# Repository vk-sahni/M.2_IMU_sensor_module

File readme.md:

# M.2 RP2350 IMU Sensor Module

A KiCad hardware design for a compact M.2 Key A sensor module built around the Raspberry Pi RP2350B. The board combines an MPU-9250 motion sensor and a BME280 environmental sensor, with UAV and ArduPilot integration as the intended use case.

> **Project status:** Work in progress. The repository contains KiCad design files only; it does not include firmware or establish plug-and-play ArduPilot compatibility. The current design has outstanding KiCad ERC/DRC violations and is not ready for fabrication or flight use.

## GitHub repository description

> KiCad design for an M.2 Key A RP2350B sensor module featuring an MPU-9250 IMU and BME280, intended for UAV and ArduPilot integration experiments.

## Design overview

- **MCU:** RP2350B
- **IMU:** MPU-9250 (accelerometer, gyroscope, and magnetometer)
- **Environmental sensor:** BME280 (pressure, temperature, and humidity)
- **Memory:** W25Q128JVSIQ QSPI flash and APS6404L PSRAM
- **Removable storage:** MicroSD card socket
- **Host connection:** M.2 Key A edge connector
- **Other interfaces:** USB Type-C, SWD test points, and status LEDs
- **Power:** On-board XC6220 3.3 V regulators

The M.2 connector schematic maps 5 V power and sensor I2C signals, including separate `SDA`/`SCL` and `MPU_SDA`/`MPU_SCL` nets. Check the full schematic and target host pinout before connecting the module; M.2 is a connector format, not a guarantee of electrical or firmware compatibility.

## ArduPilot integration

This is a hardware design intended for UAV sensor and ArduPilot integration experiments. ArduPilot supports sensor communications over protocols such as I2C, SPI, UART, and CAN, but a sensor board still needs a compatible driver/backend, wiring, and configuration. This repository does not contain that firmware integration or demonstrate that an ArduPilot flight controller can detect these sensors through this M.2 connection.

Before attempting integration, verify the M.2 host pinout and voltage levels, determine which controller owns each bus, and confirm that the target ArduPilot firmware supports the required sensors and connection arrangement. See the official [ArduPilot sensor-driver documentation](https://ardupilot.org/dev/docs/code-overview-sensor-drivers.html).

## Repository contents

- `PCIe_Pie.kicad_pro` — KiCad project settings
- `PCIe_Pie.kicad_sch` and the other `*.kicad_sch` files — top-level and hierarchical schematics
- `PCIe_Pie.kicad_pcb` — PCB layout
- `CM4IO.pretty/` — project footprint library
- `CM4IO.3dshapes/` — 3D models used by footprints
- `sym-lib-table`, `fp-lib-table` — KiCad library table configuration

## Open the design

1. Install KiCad.
2. Open `PCIe_Pie.kicad_pro`.
3. Review the complete schematic hierarchy and PCB, including the project-local footprint and 3D model libraries.

## Validation status

KiCad command-line ERC and DRC checks run against the current design reported outstanding violations, including unconnected items. Review and resolve these in KiCad before generating manufacturing files. No fabrication outputs, assembled-board test results, sensor calibration results, or flight-test results are included in this repository.

## Safety

Treat the design as experimental. Verify the schematic, PCB rules, power rails, connector orientation, and signal levels before powering hardware. Bench-test and validate the complete sensor/firmware path before any UAV flight; do not rely on this module as a flight-critical sensor without appropriate testing and failsafes.

## References

- [ArduPilot sensor drivers and supported communication protocols](https://ardupilot.org/dev/docs/code-overview-sensor-drivers.html)
- [MPU-9250 datasheet](https://invensense.tdk.com/wp-content/uploads/2015/02/PS-MPU-9250A-01-v1.1.pdf)

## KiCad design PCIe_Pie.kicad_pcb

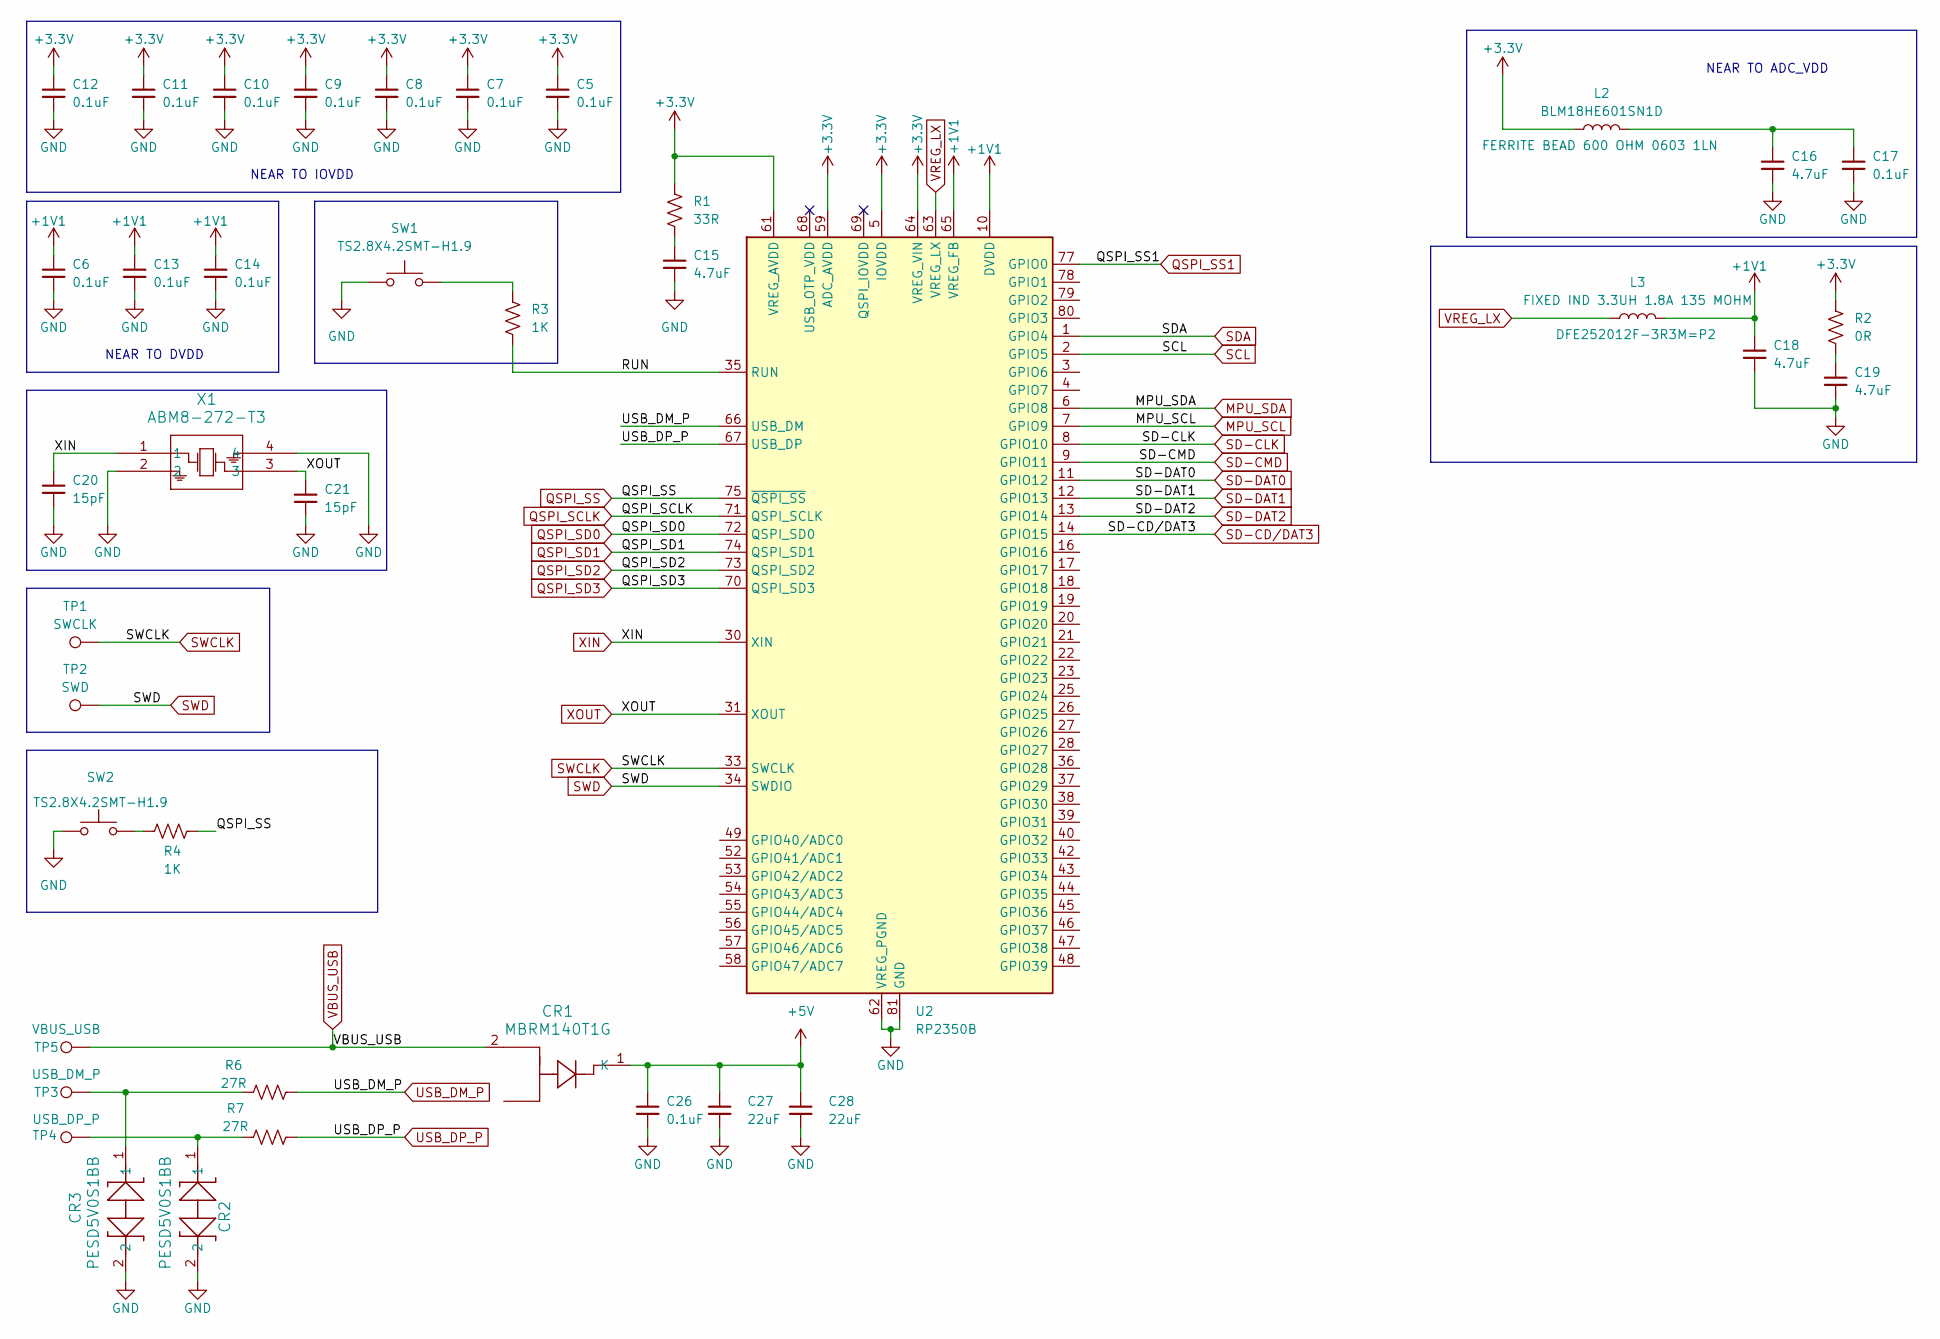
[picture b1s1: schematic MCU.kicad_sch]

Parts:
C5, C6, C7, C8, C9, C10, C11, C12, C13, C14, C17, C26: 0.1uF; C_0402_1005Metric
C15, C16, C18, C19: 4.7uF; C_0402_1005Metric
C20, C21: 15pF; C_0402_1005Metric
C27, C28: 22uF; C_0402_1005Metric
CR1: MBRM140T1G; CR_POWERMITE_457-04_ONS-L
CR2, CR3: PESD5V0S1BB; SOD523_NXP-L
L2: BLM18HE601SN1D; L_0402_1005Metric; PART FERRITE BEAD 600 OHM 0603 1LN
L3: FIXED IND 3.3UH 1.8A 135 MOHM; L_0402_1005Metric; PART DFE252012F-3R3M=P2
R1: 33R; R_0402_1005Metric
R2: 0R; R_0402_1005Metric
R3, R4: 1K; R_0402_1005Metric
R6, R7: 27R; R_0402_1005Metric
SW1, SW2: TS2.8X4.2SMT-H1.9; SW_Push_SPST_NO_Alps_SKRK
TP1: SWCLK; TestPoint_Pad_1.0x1.0mm
TP2: SWD; TestPoint_Pad_1.0x1.0mm
TP3: USB_DM_P; TestPoint_Pad_1.0x1.0mm
TP4: USB_DP_P; TestPoint_Pad_1.0x1.0mm
TP5: VBUS_USB; TestPoint_Pad_1.0x1.0mm
U2: RP2350B; QFN-80-1EP_10x10mm_P0.4mm_EP3.4x3.4mm
X1: ABM8-272-T3; ABM8-272-T3_ABR

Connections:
+1V1: C6.1, C13.1, C14.1, C18.1, L3.2, U2.10 (DVDD), U2.32 (DVDD), U2.51 (DVDD), U2.65 (VREG_FB)
+3.3V: C5.1, C7.1, C8.1, C9.1, C10.1, C11.1, C12.1, L2.1, R1.1, R2.1, U2.5 (IOVDD), U2.15 (IOVDD), U2.24 (IOVDD), U2.29 (IOVDD), U2.41 (IOVDD), U2.50 (IOVDD), U2.59 (ADC_AVDD), U2.60 (IOVDD), U2.61 (VREG_AVDD), U2.64 (VREG_VIN), U2.76 (IOVDD); also elsewhere on the board
+5V: C26.1, C27.1, C28.1, CR1.1 (K_1); also elsewhere on the board
/MCU/RUN: R3.2, U2.35 (RUN)
GND: C5.2, C6.2, C7.2, C8.2, C9.2, C10.2, C11.2, C12.2, C13.2, C14.2, C15.2, C16.2, C17.2, C18.2, C19.2, C20.2, C21.2, C26.2, C27.2, C28.2, CR2.2, CR3.2, SW1.1, SW2.1, U2.62 (VREG_PGND), U2.81 (GND), X1.2, X1.4; also elsewhere on the board
MPU_SCL: U2.7 (GPIO9); also elsewhere on the board
MPU_SDA: U2.6 (GPIO8); also elsewhere on the board
unnamed: C15.1, R1.2
unnamed: C16.1, C17.1, L2.2
unnamed: C19.1, R2.2
unnamed: CR2.1, R7.1, TP4.1 (1_1)
unnamed: CR3.1, R6.1, TP3.1 (1_1)
unnamed: R3.1, SW1.2
unnamed: R4.1, SW2.2
QSPI_SCLK: U2.71 (QSPI_SCLK); also elsewhere on the board
QSPI_SD0: U2.72 (QSPI_SD0); also elsewhere on the board
QSPI_SD1: U2.74 (QSPI_SD1); also elsewhere on the board
QSPI_SD2: U2.73 (QSPI_SD2); also elsewhere on the board
QSPI_SD3: U2.70 (QSPI_SD3); also elsewhere on the board
QSPI_SS: R4.2, U2.75 (~QSPI_SS); also elsewhere on the board
QSPI_SS1: U2.77 (GPIO0); also elsewhere on the board
SCL: U2.2 (GPIO5); also elsewhere on the board
SD-CD/DAT3: U2.14 (GPIO15); also elsewhere on the board
SD-CLK: U2.8 (GPIO10); also elsewhere on the board
SD-CMD: U2.9 (GPIO11); also elsewhere on the board
SD-DAT0: U2.11 (GPIO12); also elsewhere on the board
SD-DAT1: U2.12 (GPIO13); also elsewhere on the board
SD-DAT2: U2.13 (GPIO14); also elsewhere on the board
SDA: U2.1 (GPIO4); also elsewhere on the board
SWCLK: TP1.1 (1_1), U2.33 (SWCLK)
SWD: TP2.1 (1_1), U2.34 (SWDIO)
USB_DM_P: R6.2, U2.66 (USB_DM); also elsewhere on the board
USB_DP_P: R7.2, U2.67 (USB_DP); also elsewhere on the board
VBUS_USB: CR1.2, TP5.1 (1_1); also elsewhere on the board
VREG_LX: L3.1, U2.63 (VREG_LX)
XIN: C20.1, U2.30 (XIN), X1.1
XOUT: C21.1, U2.31 (XOUT), X1.3

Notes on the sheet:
NEAR TO ADC_VDD
NEAR TO IOVDD
NEAR TO DVDD

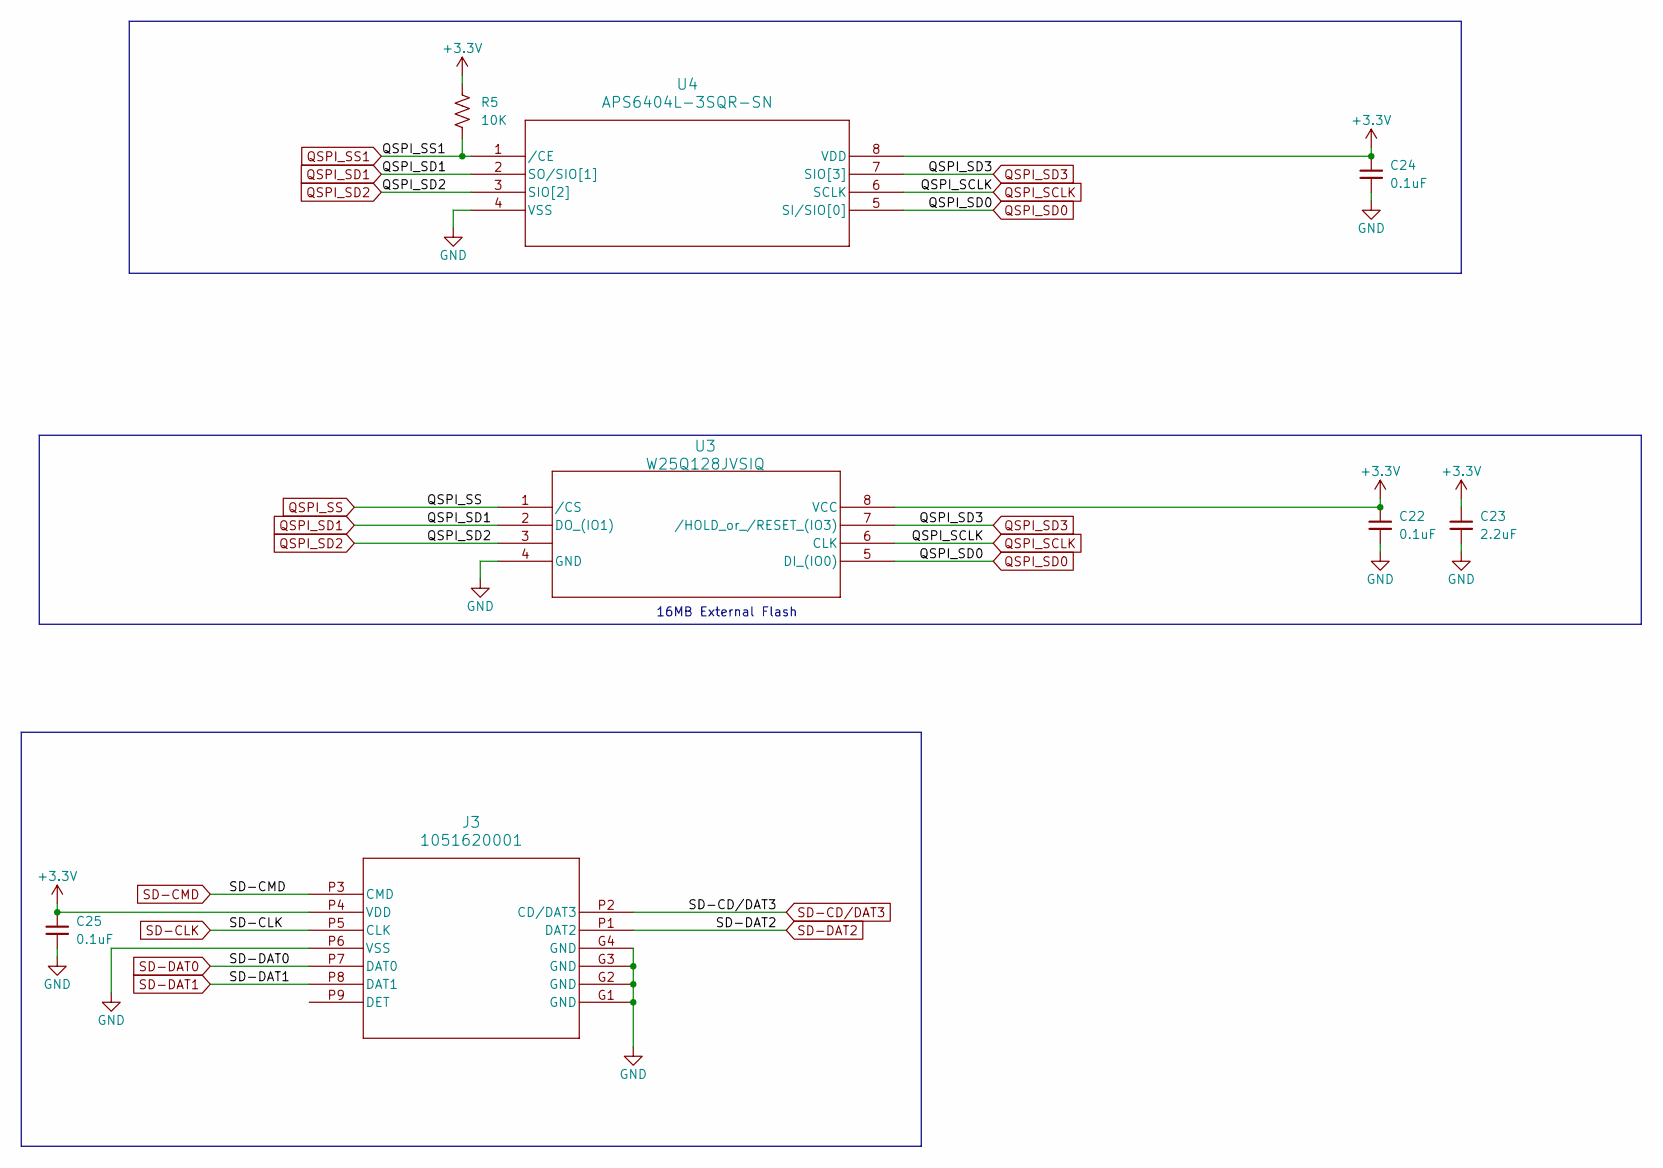
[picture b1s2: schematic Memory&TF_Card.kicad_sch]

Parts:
C22, C24, C25: 0.1uF; C_0402_1005Metric
C23: 2.2uF; C_0402_1005Metric
J3: 1051620001; 105162-0001_MOL
R5: 10K; R_0402_1005Metric
U3: W25Q128JVSIQ; SOIC_128JVSIQ_WIN-M
U4: APS6404L-3SQR-SN; APS6404L-3SQR-SN_APY-M

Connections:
+3.3V: C22.1, C23.1, C24.1, C25.1, J3.P4 (VDD), R5.1, U3.8 (VCC), U4.8 (VDD); also elsewhere on the board
GND: C22.2, C23.2, C24.2, C25.2, J3.G1 (GND), J3.G2 (GND), J3.G3 (GND), J3.G4 (GND), J3.P6 (VSS), U3.4 (GND), U4.4 (VSS); also elsewhere on the board
QSPI_SCLK: U3.6 (CLK), U4.6 (SCLK); also elsewhere on the board
QSPI_SD0: U3.5 (DI_(IO0)), U4.5 (SI/SIO[0]); also elsewhere on the board
QSPI_SD1: U3.2 (DO_(IO1)), U4.2 (SO/SIO[1]); also elsewhere on the board
QSPI_SD2: U3.3, U4.3 (SIO[2]); also elsewhere on the board
QSPI_SD3: U3.7 (/HOLD_or_/RESET_(IO3)), U4.7 (SIO[3]); also elsewhere on the board
QSPI_SS: U3.1 (/CS); also elsewhere on the board
QSPI_SS1: R5.2, U4.1 (/CE); also elsewhere on the board
SD-CD/DAT3: J3.P2 (CD/DAT3); also elsewhere on the board
SD-CLK: J3.P5 (CLK); also elsewhere on the board
SD-CMD: J3.P3 (CMD); also elsewhere on the board
SD-DAT0: J3.P7 (DAT0); also elsewhere on the board
SD-DAT1: J3.P8 (DAT1); also elsewhere on the board
SD-DAT2: J3.P1 (DAT2); also elsewhere on the board

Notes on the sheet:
16MB External Flash

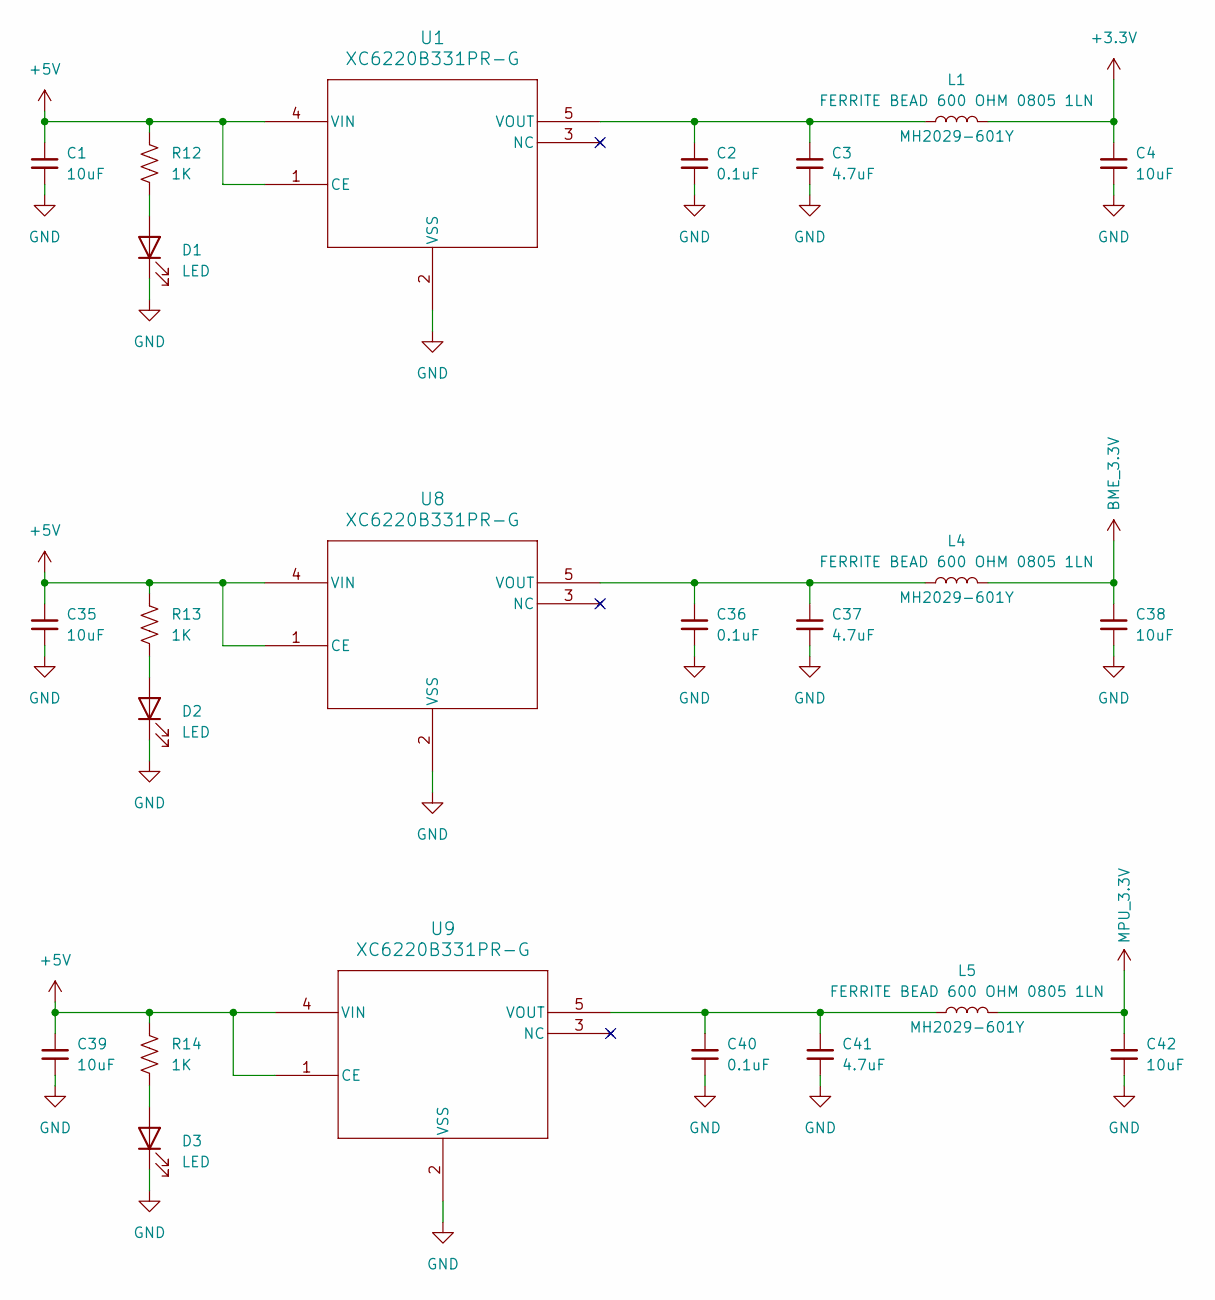
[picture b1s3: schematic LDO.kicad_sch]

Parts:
C1, C35, C39: 10uF; C_0805_2012Metric
C2, C36, C40: 0.1uF; C_0402_1005Metric
C3, C37, C41: 4.7uF; C_0402_1005Metric
C4, C38, C42: 10uF; C_0402_1005Metric
D1, D2, D3: LED; LED_0402_1005Metric
L1, L4, L5: FERRITE BEAD 600 OHM 0805 1LN; L_0402_1005Metric; Part MH2029-601Y
R12, R13, R14: 1K; R_0402_1005Metric
U1, U8, U9: XC6220B331PR-G; SOT-89-5_TOR

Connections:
+3.3V: C4.1, L1.2; also elsewhere on the board
+5V: C1.1, C35.1, C39.1, R12.1, R13.1, R14.1, U1.1 (CE), U1.4 (VIN), U8.1 (CE), U8.4 (VIN), U9.1 (CE), U9.4 (VIN); also elsewhere on the board
BME_3.3V: C38.1, L4.2; also elsewhere on the board
GND: C1.2, C2.2, C3.2, C4.2, C35.2, C36.2, C37.2, C38.2, C39.2, C40.2, C41.2, C42.2, D1.1 (K), D2.1 (K), D3.1 (K), U1.2 (VSS), U8.2 (VSS), U9.2 (VSS); also elsewhere on the board
MPU_3.3V: C42.1, L5.2; also elsewhere on the board
unnamed: D1.2 (A), R12.2
unnamed: D2.2 (A), R13.2
unnamed: D3.2 (A), R14.2
unnamed: C2.1, C3.1, L1.1, U1.5 (VOUT)
unnamed: C36.1, C37.1, L4.1, U8.5 (VOUT)
unnamed: C40.1, C41.1, L5.1, U9.5 (VOUT)

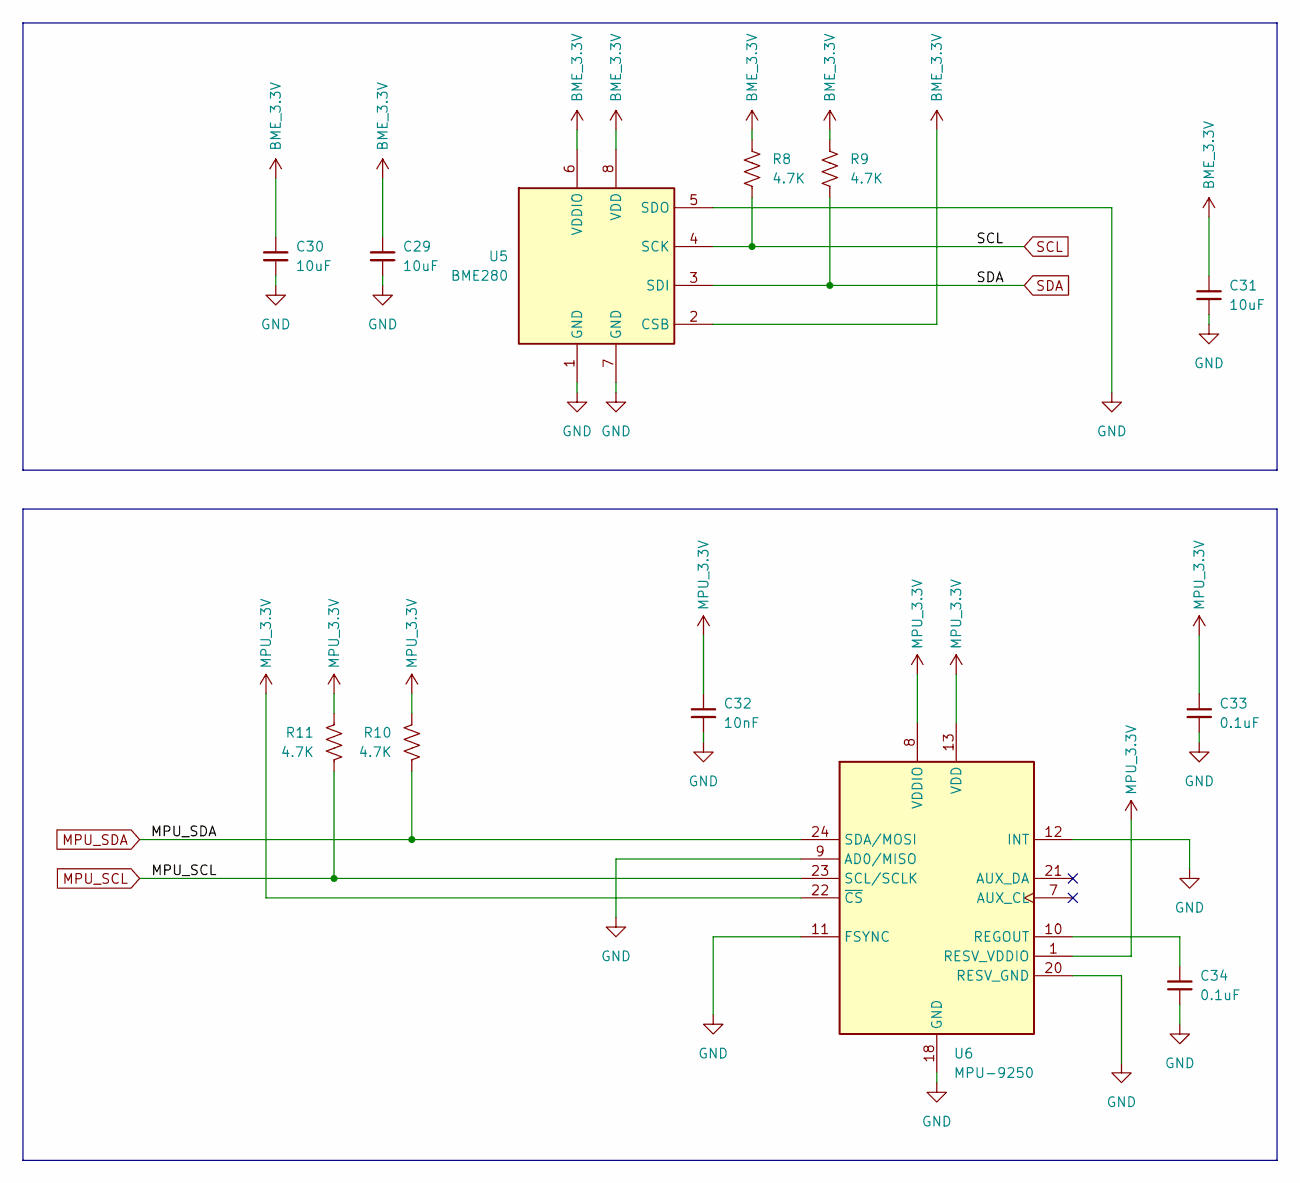
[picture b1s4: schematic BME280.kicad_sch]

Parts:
C29, C30, C31: 10uF; C_0402_1005Metric
C32: 10nF; C_0402_1005Metric
C33, C34: 0.1uF; C_0402_1005Metric
R8, R9, R10, R11: 4.7K; R_0402_1005Metric
U5: BME280; Bosch_LGA-8_2.5x2.5mm_P0.65mm_ClockwisePinNumbering
U6: MPU-9250; InvenSense_QFN-24_3x3mm_P0.4mm

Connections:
BME_3.3V: C29.1, C30.1, C31.1, R8.1, R9.1, U5.2 (CSB), U5.6 (VDDIO), U5.8 (VDD); also elsewhere on the board
GND: C29.2, C30.2, C31.2, C32.2, C33.2, C34.2, U5.1 (GND), U5.5 (SDO), U5.7 (GND), U6.9 (AD0/MISO), U6.11 (FSYNC), U6.12 (INT), U6.18 (GND), U6.20 (RESV_GND); also elsewhere on the board
MPU_3.3V: C32.1, C33.1, R10.1, R11.1, U6.1 (RESV_VDDIO), U6.8 (VDDIO), U6.13 (VDD), U6.22 (~CS); also elsewhere on the board
MPU_SCL: R11.2, U6.23 (SCL/SCLK); also elsewhere on the board
MPU_SDA: R10.2, U6.24 (SDA/MOSI); also elsewhere on the board
unnamed: C34.1, U6.10 (REGOUT)
SCL: R8.2, U5.4 (SCK); also elsewhere on the board
SDA: R9.2, U5.3 (SDI); also elsewhere on the board

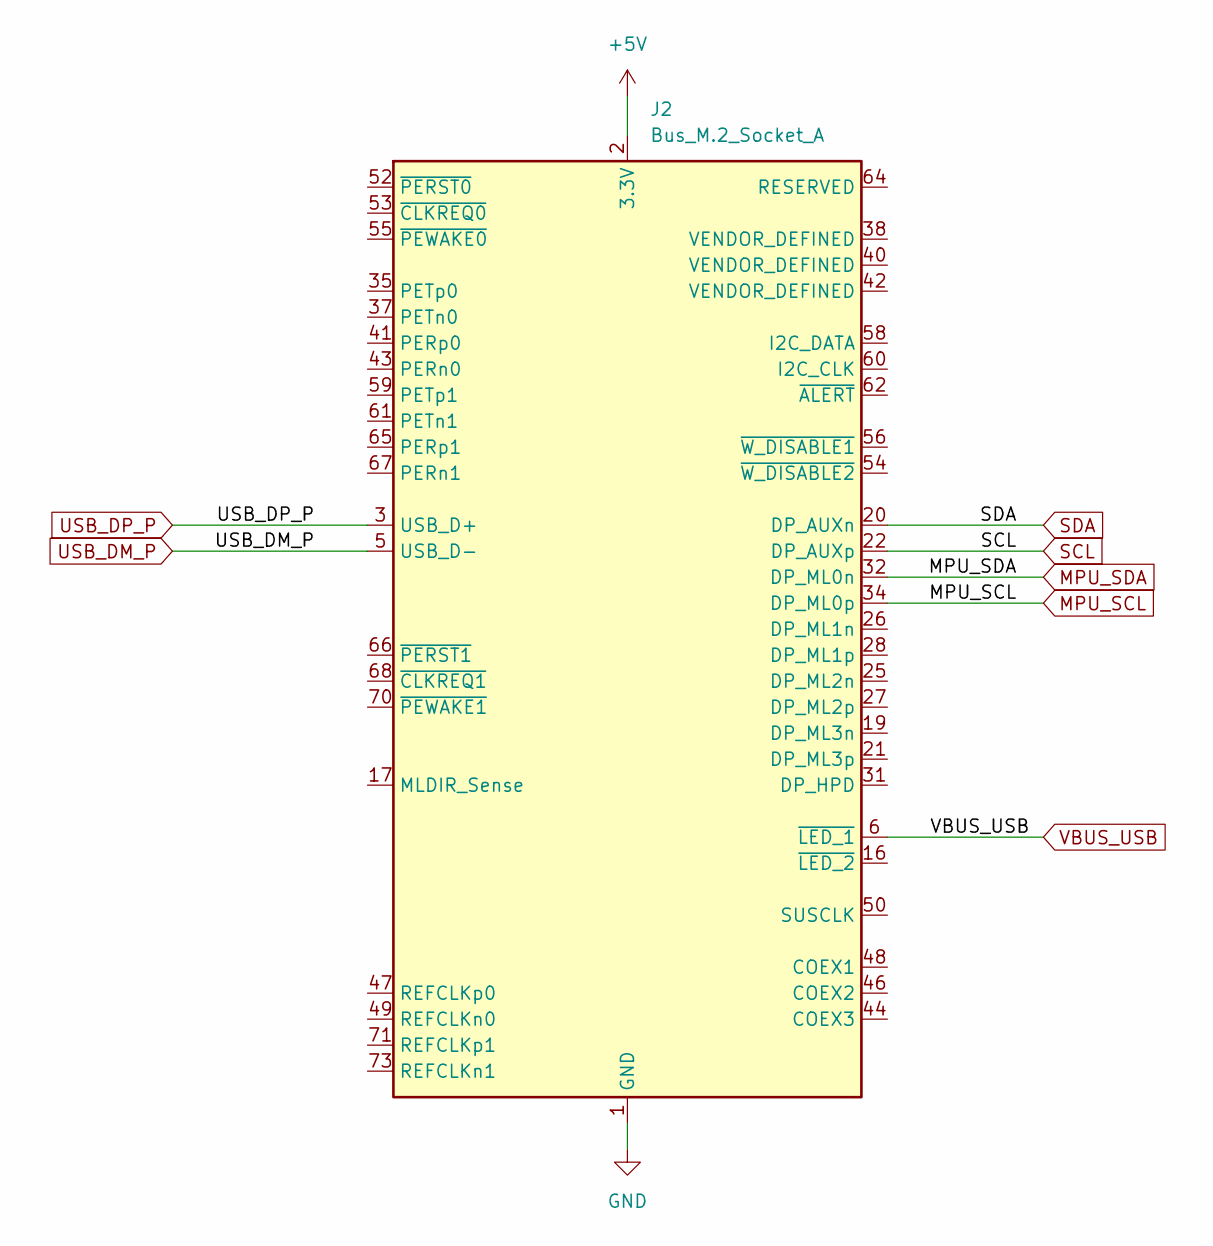
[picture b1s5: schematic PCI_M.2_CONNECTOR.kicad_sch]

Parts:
J2: Bus_M.2_Socket_A; M.2_3030-xx-A

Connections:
+5V: J2.2 (3.3V), J2.4 (3.3V), J2.72 (3.3V), J2.74 (3.3V); also elsewhere on the board
GND: J2.1 (GND), J2.7 (GND), J2.18 (GND), J2.23 (GND), J2.24 (GND), J2.29 (GND), J2.30 (GND), J2.33 (GND), J2.36 (GND), J2.39 (GND), J2.45 (GND), J2.51 (GND), J2.57 (GND), J2.63 (GND), J2.69 (GND), J2.75 (GND); also elsewhere on the board
MPU_SCL: J2.34 (DP_ML0p); also elsewhere on the board
MPU_SDA: J2.32 (DP_ML0n); also elsewhere on the board
SCL: J2.22 (DP_AUXp); also elsewhere on the board
SDA: J2.20 (DP_AUXn); also elsewhere on the board
USB_DM_P: J2.5 (USB_D-); also elsewhere on the board
USB_DP_P: J2.3 (USB_D+); also elsewhere on the board
VBUS_USB: J2.6 (~LED_1); also elsewhere on the board

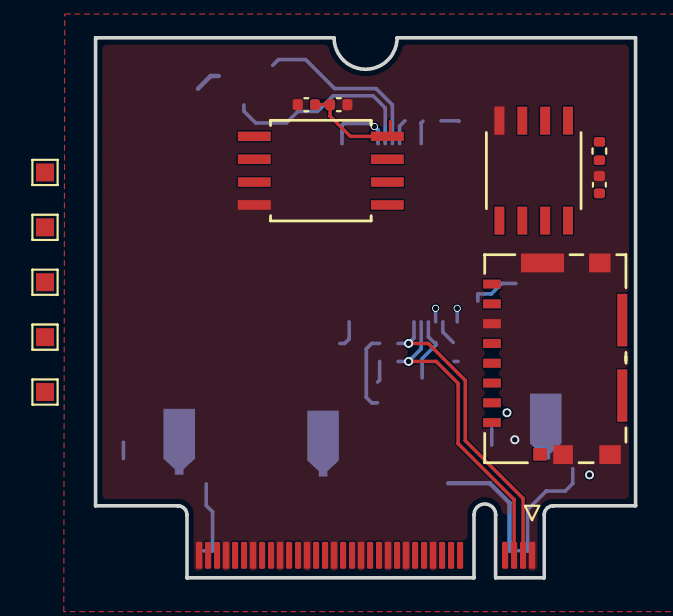
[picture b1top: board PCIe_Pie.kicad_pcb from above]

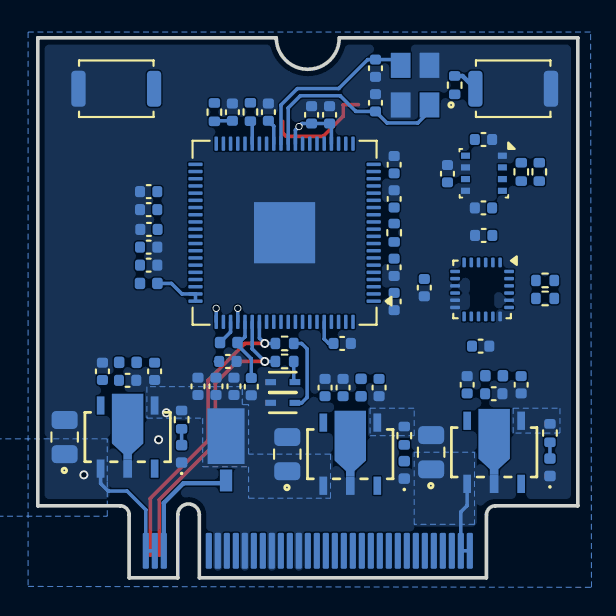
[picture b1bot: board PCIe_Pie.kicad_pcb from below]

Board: 4 copper layers, 30.0 x 30.0 mm, 85 parts (72 on the bottom side), 46 nets.
